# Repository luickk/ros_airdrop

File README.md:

# ROS AirDrop

AirDrop is an autonomous Drone system, based on the open source [dji naza interface interface](https://github.com/MrGrimod/dji_naza_interface_c-). It's ment to deliver payloads quick and easy without relying on custom or second hand flight controller implementations. Instead, it relies on [an interface](https://github.com/MrGrimod/dji_naza_interface_c-), for any flight controller (currently using the DJI Naza V2), which allows the system to operate safe and predictable as well as open source.
It consists of a number of ROS packages containing the core and mission critical nodes. The Web Interface for remote controle can be found [here](https://github.com/MrGrimod/web_airdrop).

## Video

https://www.youtube.com/watch?v=QzOBck26Hko

### Packages

- Command & Control (CC) node (planned) <br>
The CC node handles all requests that require the drone to move or change position <br> in physical space by offering ROS services. It also manages all state variables, which makes it to the most important package.

- GPS Node <br>
Node that constantly publishes GPS position data under the `gps_raw` topic. The data is read via the raspberries serial port and comes directly from the GPS Unit's serial output(tx) which is also linked to the Naza V2.
The original code to decode the gps protocol is from pawelsky and has been adapted to raspberry c++ standards and can be found [here](https://www.rcgroups.com/forums/showthread.php?1995704-DJI-NAZA-GPS-communication-protocol-NazaDecoder-Arduino-library)

- MN Node <br>
Node that parses and then runs missions(files) by calling services <br> provided by CC node.

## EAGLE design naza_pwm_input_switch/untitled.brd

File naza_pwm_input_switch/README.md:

# ROS AirDrop - PWM input switch 

The PCB is designed to act as an switch, to switch between the Raspberry Pi(or PWM Driver board) or the receiver as input source for the Naza-flight-controller.
In other words, it's ensuring that I can switch all the time, independently from the autonomous system(Raspberry Pi), to the 
receiver as input source for the flight controller, to take over controll myself, and the other way around.

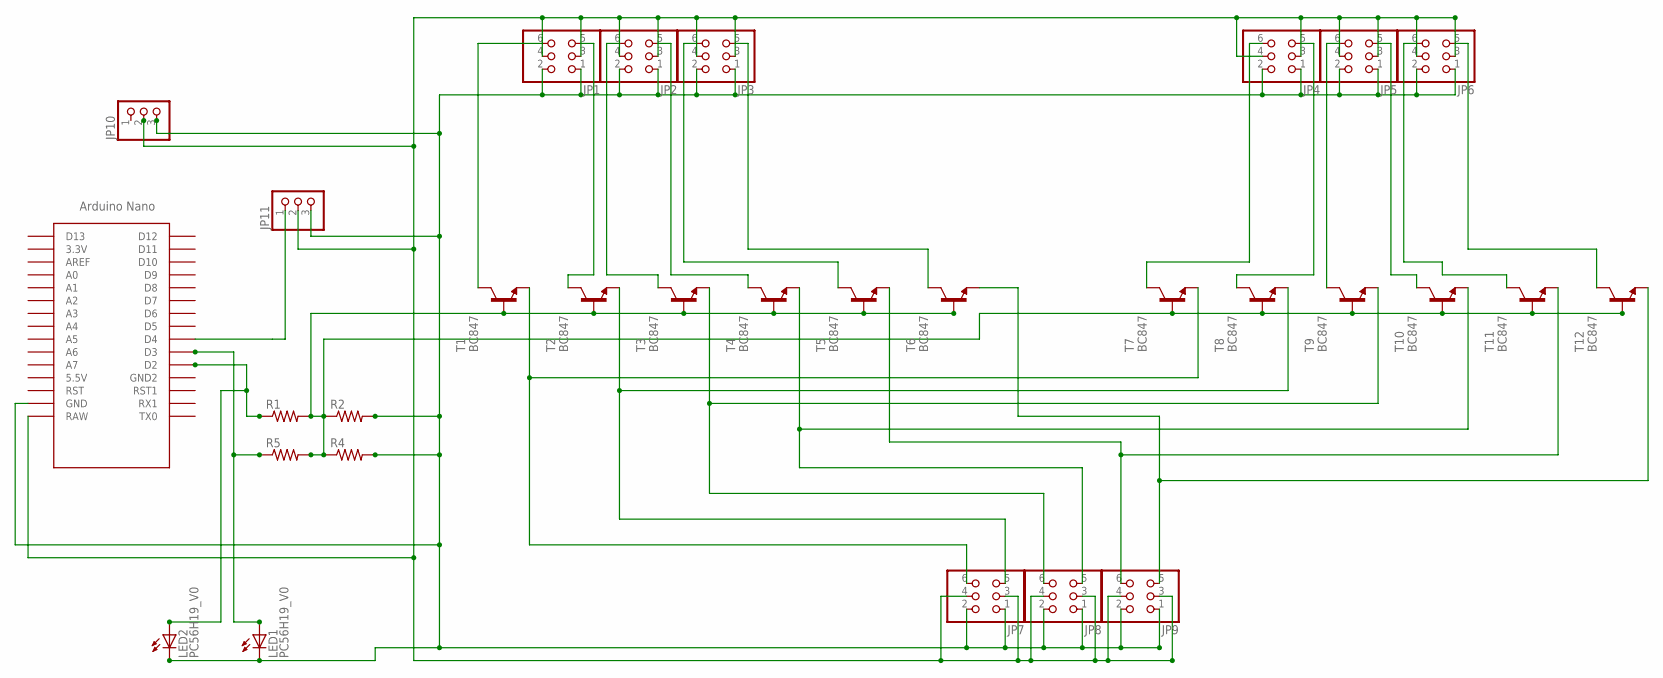
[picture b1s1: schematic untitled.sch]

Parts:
JP1, JP2, JP3, JP4, JP5, JP6, JP7, JP8, JP9: PINHD-2X3; 2X03
JP10, JP11: PINHD-1X3; 1X03
LED1, LED2: PC56H19_V0
R1, R2, R4, R5: R-US_0207/10; 0207/10
T1, T2, T3, T4, T5, T6, T7, T8, T9, T10, T11, T12: BC847; SOT23
U$1: NANO

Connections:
unnamed: JP1.6, T1.3 (C)
unnamed: JP1.5, T2.3 (C)
unnamed: JP2.6, T3.3 (C)
unnamed: JP2.5, T4.3 (C)
unnamed: JP3.6, T5.3 (C)
unnamed: JP3.5, T6.3 (C)
unnamed: JP4.6, T7.3 (C)
unnamed: JP4.5, T8.3 (C)
unnamed: JP5.6, T9.3 (C)
unnamed: JP5.5, T10.3 (C)
unnamed: JP6.6, T11.3 (C)
unnamed: JP6.5, T12.3 (C)
unnamed: JP1.1, JP1.2, JP2.1, JP2.2, JP3.1, JP3.2, JP4.1, JP4.2, JP5.1, JP5.2, JP6.1, JP6.2, JP7.1, JP7.2, JP8.1, JP8.2, JP9.1, JP9.2, JP10.3, JP11.3, LED1.1 (C), LED1.3 (C), LED2.1 (C), LED2.3 (C), R2.2, R4.2, U$1.GND
unnamed: JP11.1, U$1.D4
unnamed: LED2.2 (A), LED2.4 (A), R1.1, U$1.D2
unnamed: JP9.6, T5.2 (E), T11.2 (E)
unnamed: JP7.6, T1.2 (E), T7.2 (E)
unnamed: JP7.5, T2.2 (E), T8.2 (E)
unnamed: JP8.6, T3.2 (E), T9.2 (E)
unnamed: JP8.5, T4.2 (E), T10.2 (E)
unnamed: JP9.5, T6.2 (E), T12.2 (E)
unnamed: LED1.2 (A), LED1.4 (A), R5.1, U$1.D3
unnamed: R4.1, R5.2, T7.1 (B), T8.1 (B), T9.1 (B), T10.1 (B), T11.1 (B), T12.1 (B)
unnamed: R1.2, R2.1, T1.1 (B), T2.1 (B), T3.1 (B), T4.1 (B), T5.1 (B), T6.1 (B)
unnamed: JP1.3, JP1.4, JP2.3, JP2.4, JP3.3, JP3.4, JP4.3, JP4.4, JP5.3, JP5.4, JP6.3, JP6.4, JP7.3, JP7.4, JP8.3, JP8.4, JP9.3, JP9.4, JP10.2, JP11.2, U$1.RAW

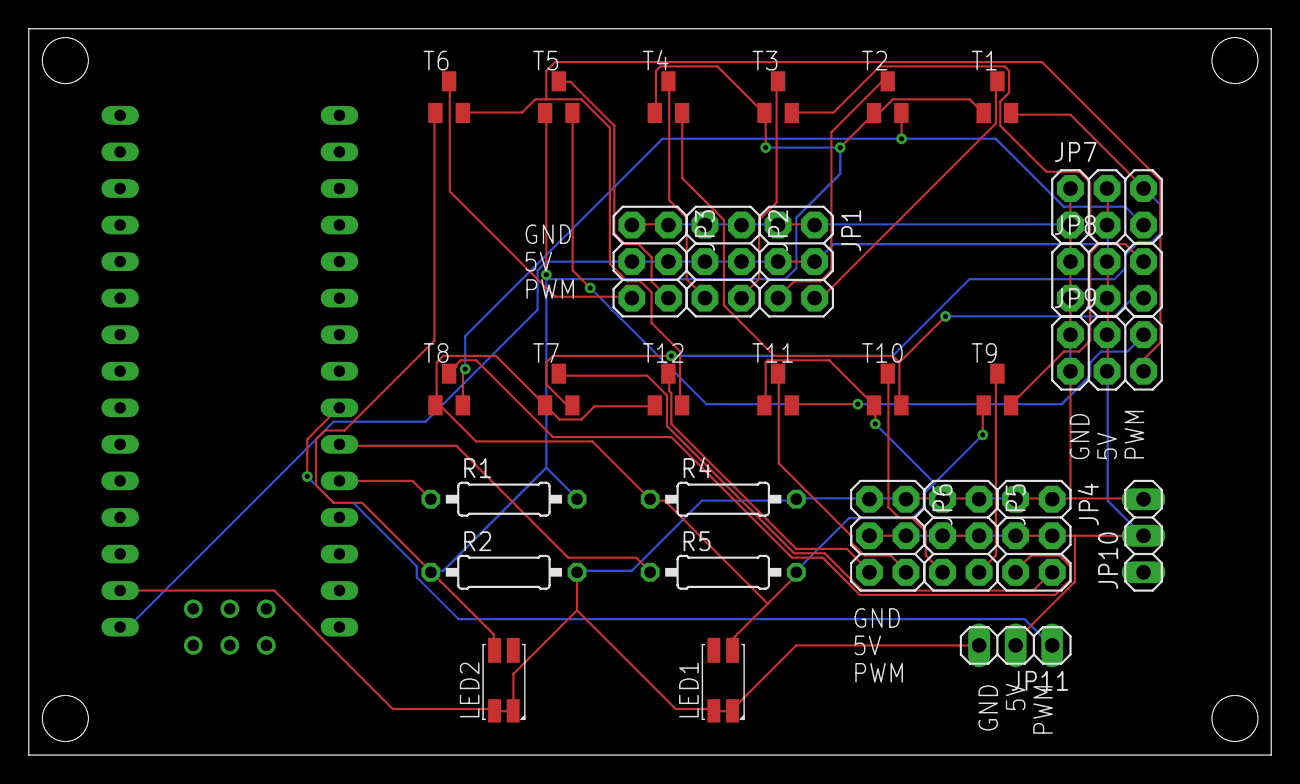
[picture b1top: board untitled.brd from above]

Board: 2 copper layers, 86.3 x 50.5 mm, 30 parts (0 on the bottom side), 25 nets.

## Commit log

2018-10-08 init
2018-10-08 adding readme & adding gps node
2018-10-08 adding gps_raw msg
2018-10-16 adding PWM input switch, PCB files
2018-10-17 adjusting PCB-pwm-input-switch led voltage
2018-10-18 adding command and control node (cc node) and startup hierarchie
2018-10-20 adding pwm_switch arduino project
2018-10-20 adding basic services for cc node
2018-10-22 adding cc service inits
2018-11-13 including dji naza lib in cc_node
2018-11-13 adding flightstates to cc_nodes
2018-11-15 adding rc_node (remote control node/cli)
2018-11-16 adding mission engine node
2018-11-22 adding mission command parsing
2018-11-23 completing mission command parsing
2018-11-25 adding service calls and cleaning up syntax
2018-11-25 correcting wrong var assignments in cc node
2018-12-05 adding rosbridge pkg for web-interface
2018-12-05 adding rosbridge to cc launch file
2018-12-08 adding take off position memory and service
2018-12-08 adding shared pointer for node handle
2018-12-11 adding mission_list service to mn node
2018-12-11 adding diagnostics package and adding cc node local functions
2018-12-11 removing break
2018-12-14 editing err_codes.md
2018-12-23 adding gps failure recovery
2018-12-26 adding landing phase status
2018-12-27 adding battery talker node
2019-01-02 building fly_to operation
2019-01-05 Create LICENSE
2019-01-05 completing fly_to operation
2019-01-09 resetting flight states in landing method & moving logging calls to cc node
2019-01-30 adding debugging state and state reset func
2019-01-30 fixing comp issue
2019-02-02 fixing debug state
2019-02-04 adding cc drone state publisher
2019-02-06 reducing publisher buffering
2019-02-06 decreasing state publisher loop rate
2019-02-10 fixing turnto op problem and added state conf
2019-02-10 fixing list_missions service
2019-02-12 fixing ros_info integer printing
2019-02-13 adding in_mission support
2019-02-13 adding in_operation state
2019-02-14 adding hover & wait mission commands
2019-05-14 adding video
2019-07-14 hotfixing flyto mission command arg length check

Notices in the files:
parts and their libraries:
SparkFun: Licensing: CC v3.0 Share-Alike You are welcome to use this library for commercial purposes.
